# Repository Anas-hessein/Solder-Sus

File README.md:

# Solder-Sus
PCB that I made with love and passion. 

## Schematic

## PCB

## BOM
1 LED
2 Resistors
1 Photoresistor
1 Capacitor
1 Button
1 Vibration Motor
2 Transistors (NPN)
2 Diodes
1 Battery charger 

## Hi

Made by @Anaskiiled on slack :]

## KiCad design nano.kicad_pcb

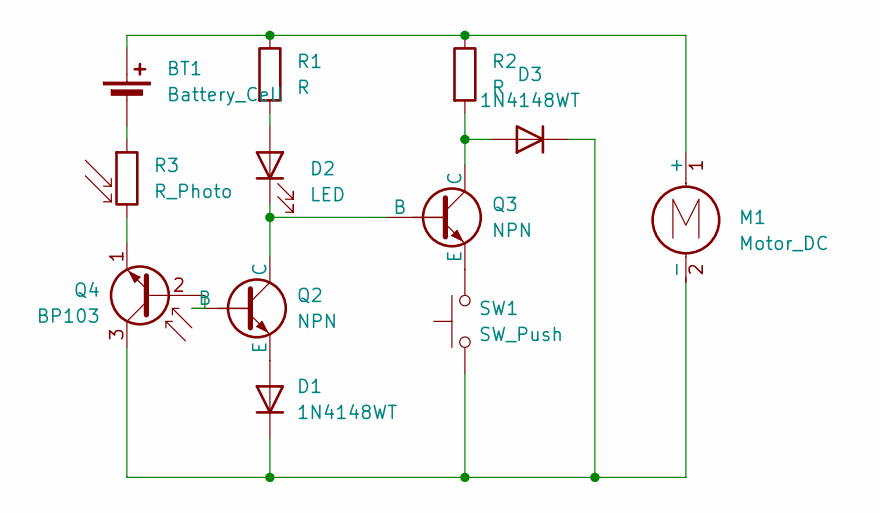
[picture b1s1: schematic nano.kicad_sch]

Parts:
BT1: Battery_Cell; BatteryHolder_Keystone_3034_1x20mm
D1, D3: 1N4148WT; D_SOD-523
D2: LED; LED_D5.0mm
M1: Motor_DC; Vybronics_VZ30C1T8219732L
Q2, Q3: NPN; TO-92L_HandSolder
Q4: BP103; TO-18-3_Lens
R1, R2: R; R_Axial_DIN0207_L6.3mm_D2.5mm_P7.62mm_Horizontal
R3: R_Photo; R_LDR_5.1x4.3mm_P3.4mm_Vertical
SW1: SW_Push; SW_PUSH_6mm

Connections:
unnamed: BT1.1 (+), M1.1 (+), R1.1, R2.1
unnamed: BT1.2 (-), R3.1
unnamed: D1.2 (A), Q2.3 (E)
unnamed: D1.1 (K), D3.1 (K), M1.2 (-), Q4.3 (C), SW1.1
unnamed: D2.2 (A), R1.2
unnamed: D2.1 (K), Q2.1 (C), Q3.2 (B)
unnamed: D3.2 (A), Q3.1 (C), R2.2
unnamed: Q2.2 (B), Q4.2 (B)
unnamed: Q3.3 (E), SW1.2
unnamed: Q4.1 (E), R3.2

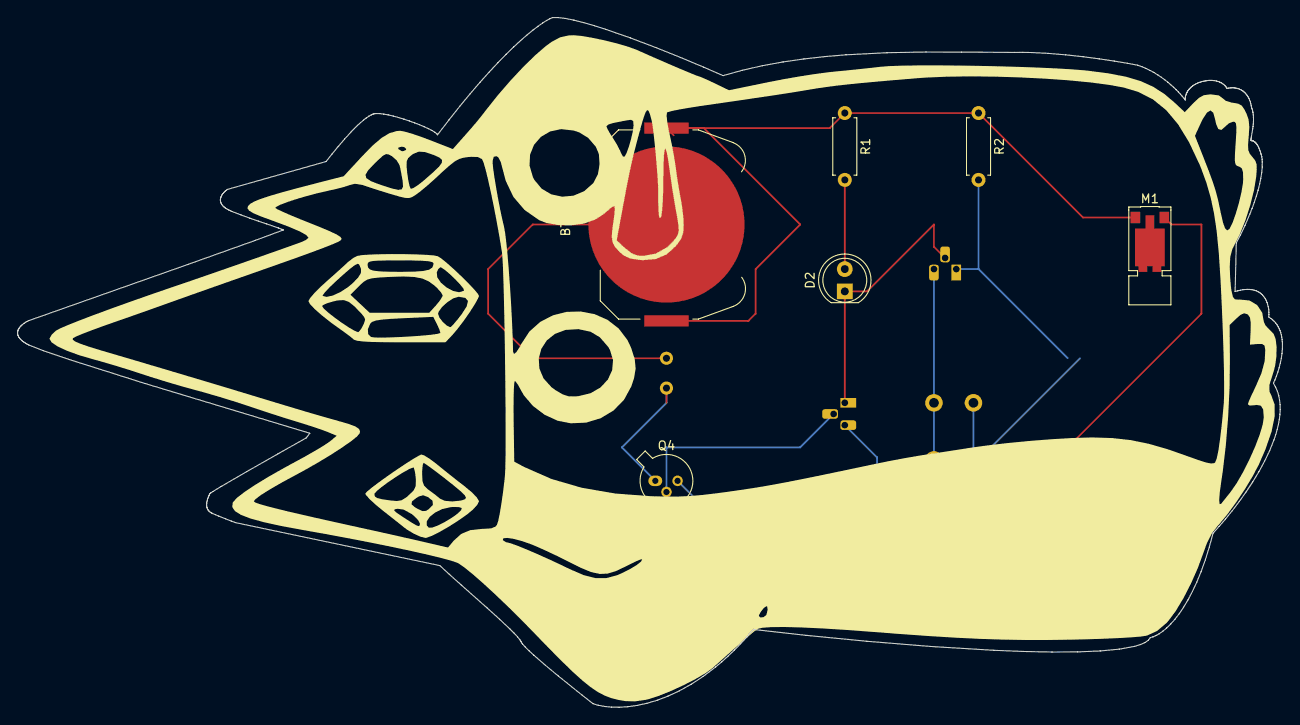
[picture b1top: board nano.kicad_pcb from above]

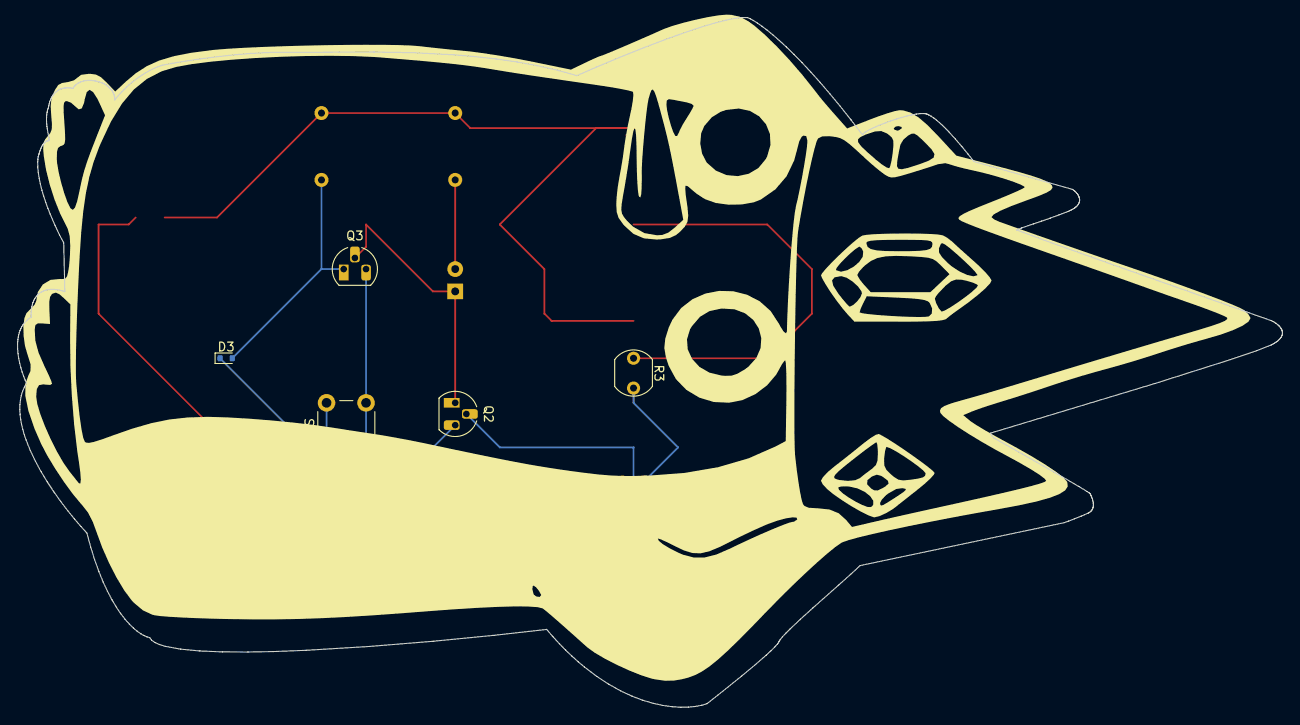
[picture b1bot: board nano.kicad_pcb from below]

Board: 2 copper layers, 144.1 x 78.6 mm, 12 parts (6 on the bottom side), 10 nets.

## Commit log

2025-06-08 finally
2025-06-08 Final
2025-06-09 the last
2025-06-09 Last README.md
